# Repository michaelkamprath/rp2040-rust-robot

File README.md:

# RP2040 Rust Robot
Robot controller code in Rust for a two wheel robot driven by a _Raspberry Pi Pico (RP2040)_.

_This is a Work in Progress_

This project is a fork of the [rp2040-project-template](https://github.com/rp-rs/rp2040-project-template). See the template's [README.md](https://github.com/rp-rs/rp2040-project-template/blob/main/README.md) for details on how to build the code found here for the RP2040.

## Notes
Uses [rusty-hook](https://github.com/swellaby/rusty-hook) for precommit hooks.

## Hardware

## License

The contents of this repository are dual-licensed under the _MIT OR Apache
2.0_ License. That means you can chose either the MIT licence or the
Apache-2.0 licence when you re-use this code. See `MIT` or `APACHE2.0` for more
information on each specific licence.

Any submissions to this project (e.g. as Pull Requests) must be made available
under these terms.

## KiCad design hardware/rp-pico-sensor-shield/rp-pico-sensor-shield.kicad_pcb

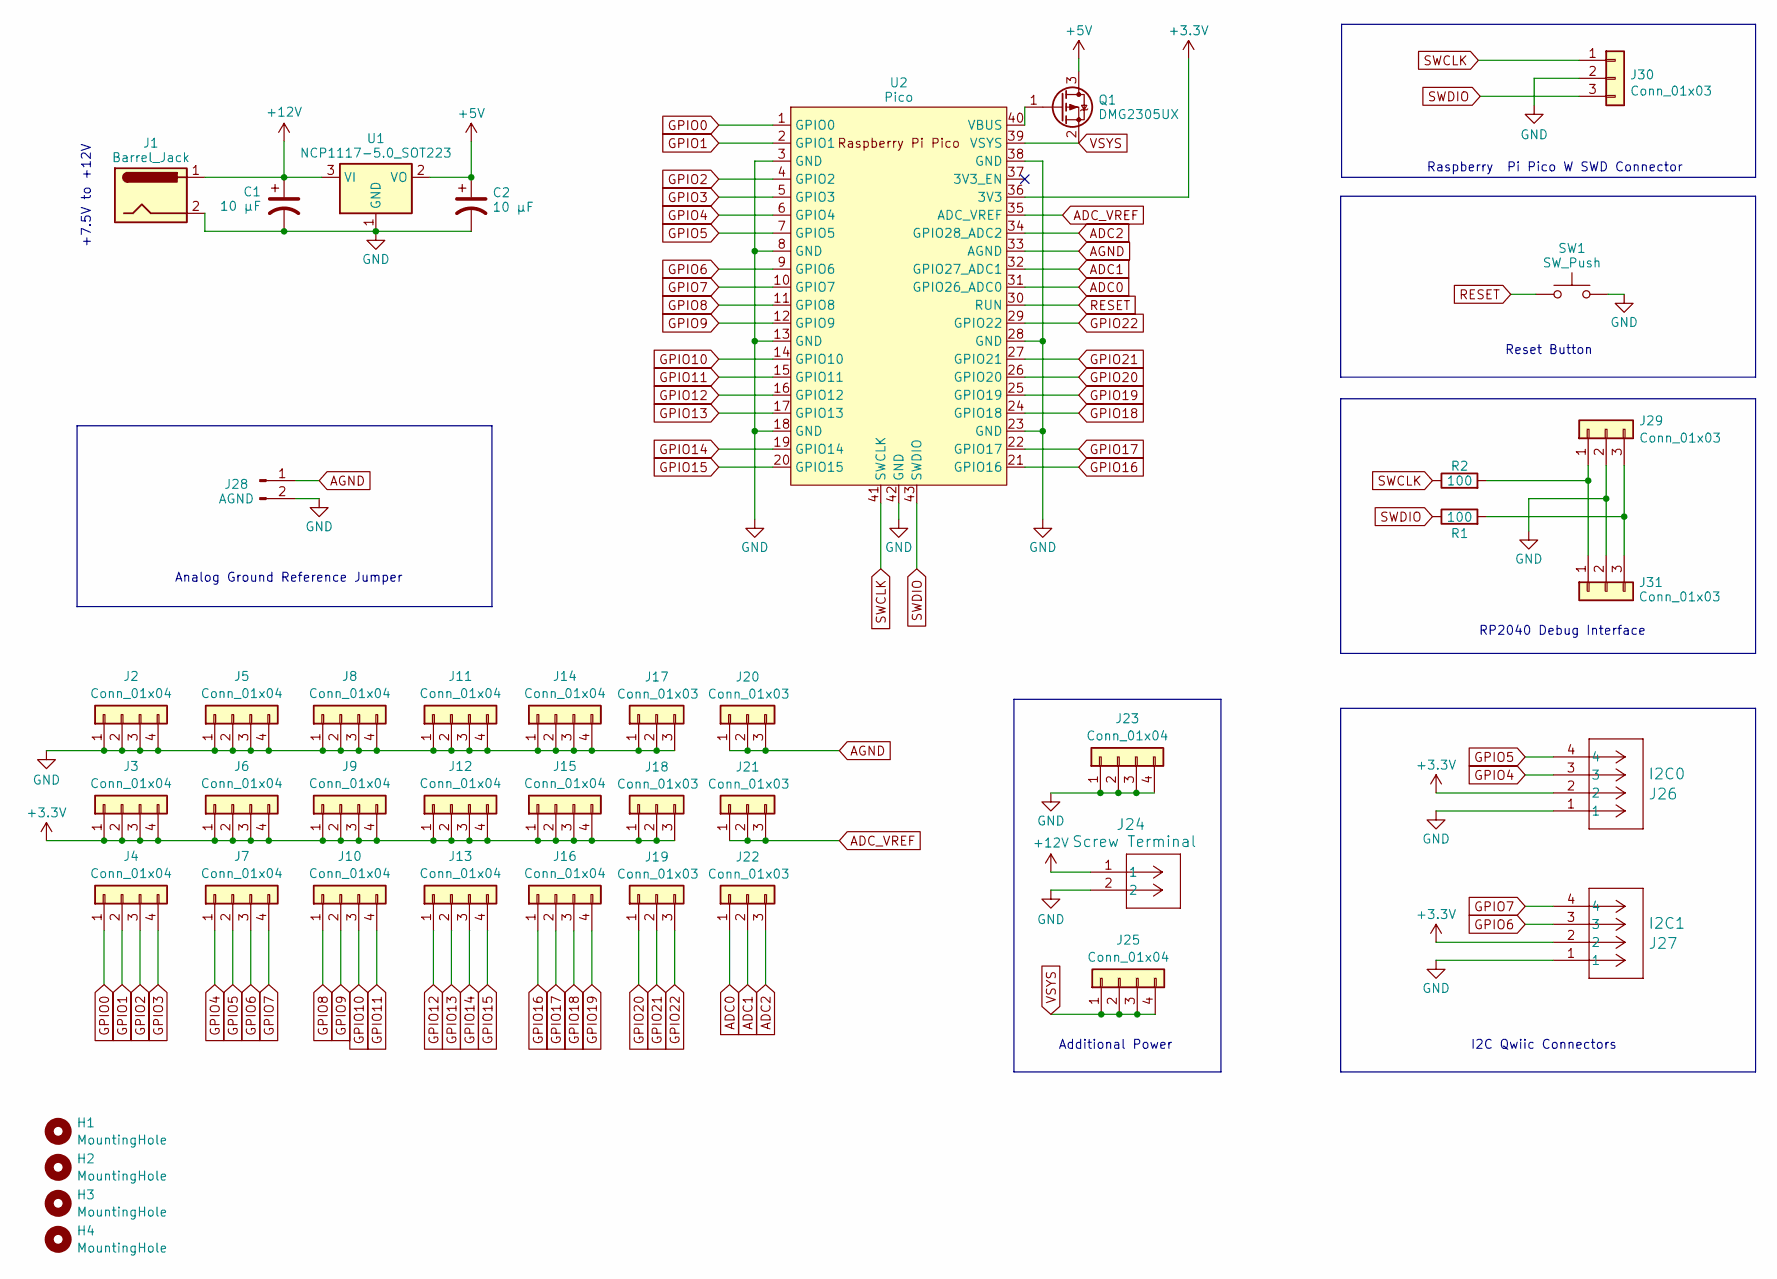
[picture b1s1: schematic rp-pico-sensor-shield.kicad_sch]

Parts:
C1, C2: 10 µF; C_1206_3216Metric_Pad1.33x1.80mm_HandSolder
H1, H2, H3, H4: MountingHole; MountingHole_3.2mm_M3_ISO7380_Pad
J1: Barrel_Jack; BarrelJack_Horizontal
J2, J3, J4, J5, J6, J7, J8, J9, J10, J11, J12, J13, J14, J15, J16, J23, J25: Conn_01x04; PinHeader_1x04_P2.54mm_Vertical
J17, J18, J19, J20, J21, J22: Conn_01x03; PinHeader_1x03_P2.54mm_Vertical
J24: Screw Terminal; CONN2_1760510000_WED
J26: I2C0; CONN_SM04B-SRSS-TB_JST
J27: I2C1; CONN_SM04B-SRSS-TB_JST
J28: AGND; PinHeader_1x02_P2.54mm_Vertical
J29: Conn_01x03; JST_SH_BM03B-SRSS-TB_1x03-1MP_P1.00mm_Vertical
J30: Conn_01x03; PinHeader_1x03_P1.00mm_Vertical
J31: Conn_01x03; PinHeader_1x03_P2.54mm_Horizontal
Q1: DMG2305UX; SOT-23
R1, R2: 100; R_1206_3216Metric_Pad1.30x1.75mm_HandSolder
SW1: SW_Push; SW_PUSH_6mm
U1: NCP1117-5.0_SOT223; SOT-223-3_TabPin2
U2: Pico; RPi_Pico_SMD_TH

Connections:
+3.3V: J3.1, J3.2, J3.3, J3.4, J6.1, J6.2, J6.3, J6.4, J9.1, J9.2, J9.3, J9.4, J12.1, J12.2, J12.3, J12.4, J15.1, J15.2, J15.3, J15.4, J18.1, J18.2, J18.3, J26.2, J27.2, U2.36 (3V3)
+5V: C2.1, Q1.3 (D), U1.2 (VO)
+12V: C1.1, J1.1, J24.1, U1.3 (VI)
ADC0: J22.1, U2.31 (GPIO26_ADC0)
ADC1: J22.2, U2.32 (GPIO27_ADC1)
ADC2: J22.3, U2.34 (GPIO28_ADC2)
ADC_VREF: J21.1, J21.2, J21.3, U2.35 (ADC_VREF)
AGND: J20.1, J20.2, J20.3, J28.1, U2.33 (AGND)
GND: C1.2, C2.2, J1.2, J2.1, J2.2, J2.3, J2.4, J5.1, J5.2, J5.3, J5.4, J8.1, J8.2, J8.3, J8.4, J11.1, J11.2, J11.3, J11.4, J14.1, J14.2, J14.3, J14.4, J17.1, J17.2, J17.3, J23.1, J23.2, J23.3, J23.4, J24.2, J26.1, J27.1, J28.2, J29.2, J30.2, J31.2, SW1.2, U1.1 (GND), U2.3 (GND), U2.8 (GND), U2.13 (GND), U2.18 (GND), U2.23 (GND), U2.28 (GND), U2.38 (GND), U2.42 (GND)
GPIO0: J4.1, U2.1 (GPIO0)
GPIO1: J4.2, U2.2 (GPIO1)
GPIO2: J4.3, U2.4 (GPIO2)
GPIO3: J4.4, U2.5 (GPIO3)
GPIO4: J7.1, J26.3, U2.6 (GPIO4)
GPIO5: J7.2, J26.4, U2.7 (GPIO5)
GPIO6: J7.3, J27.3, U2.9 (GPIO6)
GPIO7: J7.4, J27.4, U2.10 (GPIO7)
GPIO8: J10.1, U2.11 (GPIO8)
GPIO9: J10.2, U2.12 (GPIO9)
GPIO10: J10.3, U2.14 (GPIO10)
GPIO11: J10.4, U2.15 (GPIO11)
GPIO12: J13.1, U2.16 (GPIO12)
GPIO13: J13.2, U2.17 (GPIO13)
GPIO14: J13.3, U2.19 (GPIO14)
GPIO15: J13.4, U2.20 (GPIO15)
GPIO16: J16.1, U2.21 (GPIO16)
GPIO17: J16.2, U2.22 (GPIO17)
GPIO18: J16.3, U2.24 (GPIO18)
GPIO19: J16.4, U2.25 (GPIO19)
GPIO20: J19.1, U2.26 (GPIO20)
GPIO21: J19.2, U2.27 (GPIO21)
GPIO22: J19.3, U2.29 (GPIO22)
unnamed: J29.1, J31.1, R2.2
unnamed: J29.3, J31.3, R1.2
unnamed: Q1.1 (G), U2.40 (VBUS)
RESET: SW1.1, U2.30 (RUN)
SWCLK: J30.1, R2.1, U2.41 (SWCLK)
SWDIO: J30.3, R1.1, U2.43 (SWDIO)
VSYS: J25.1, J25.2, J25.3, J25.4, Q1.2 (S), U2.39 (VSYS)

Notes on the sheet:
I2C Qwiic Connectors
Reset Button
Additional Power
+7.5V to +12V
RP2040 Debug Interface
Analog Ground Reference Jumper
Raspberry Pi Pico W SWD Connector

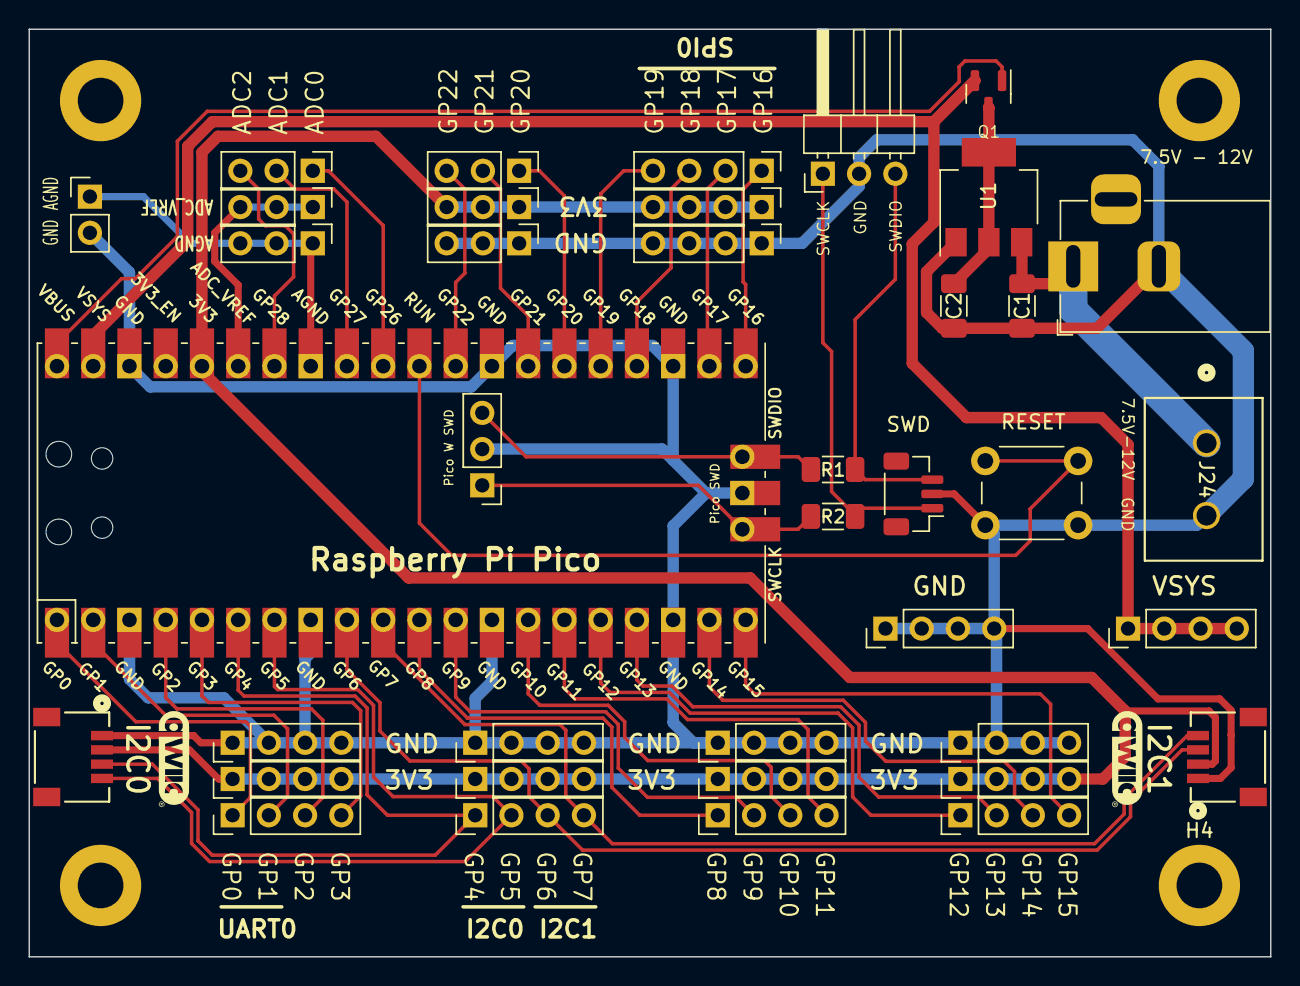
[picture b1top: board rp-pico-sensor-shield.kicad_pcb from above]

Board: 2 copper layers, 87.0 x 65.0 mm, 43 parts (0 on the bottom side), 39 nets.

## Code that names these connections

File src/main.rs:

#![no_std]
#![no_main]
mod driver;
mod model;
mod robot;
mod system;

use core::cell::RefCell;
use critical_section::Mutex;
use defmt::{info, panic};
use defmt_rtt as _;
use panic_probe as _;

use crate::robot::Robot;
use bsp::{
    entry,
    hal::fugit::HertzU32,
    hal::{
        clocks::{init_clocks_and_plls, Clock},
        gpio::{bank0::Gpio25, FunctionI2C, FunctionSioOutput, Pin, PullNone, PullUp},
        multicore::Multicore,
        pac,
        pwm::Slices,
        sio::Sio,
        watchdog::Watchdog,
    },
};
use driver::Driver;
use rp_pico::{self as bsp};
use system::millis::init_millis;
extern crate alloc;

use embedded_alloc::TlsfHeap as Heap;
#[global_allocator]
static HEAP: Heap = Heap::empty();

static GLOBAL_LED_PIN: Mutex<RefCell<Option<Pin<Gpio25, FunctionSioOutput, PullNone>>>> =
    Mutex::new(RefCell::new(None));

#[entry]
fn main() -> ! {
    // Initialize the allocator BEFORE you use it
    {
        use core::mem::MaybeUninit;
        const HEAP_SIZE: usize = 4048;
        static mut HEAP_MEM: [MaybeUninit<u8>; HEAP_SIZE] = [MaybeUninit::uninit(); HEAP_SIZE];
        #[allow(static_mut_refs)]
        unsafe {
            HEAP.init(HEAP_MEM.as_ptr() as usize, HEAP_SIZE)
        }
    }

    info!("Program start");
    let mut pac = pac::Peripherals::take().unwrap();
    let _core = pac::CorePeripherals::take().unwrap();
    let mut watchdog = Watchdog::new(pac.WATCHDOG);
    let mut sio = Sio::new(pac.SIO);

    // External high-speed crystal on the pico board is 12Mhz
    let external_xtal_freq_hz = 12_000_000u32;
    let clocks = init_clocks_and_plls(
        external_xtal_freq_hz,
        pac.XOSC,
        pac.CLOCKS,
        pac.PLL_SYS,
        pac.PLL_USB,
        &mut pac.RESETS,
        &mut watchdog,
    )
    .ok()
    .unwrap();
    let sys_freq = clocks.system_clock.freq();

    let pins = bsp::Pins::new(
        pac.IO_BANK0,
        pac.PADS_BANK0,
        sio.gpio_bank0,
        &mut pac.RESETS,
    );
    critical_section::with(|cs| {
        GLOBAL_LED_PIN
            .borrow(cs)
            .replace(Some(pins.led.reconfigure()));
    });

    // init timer and millis
    let mut timer = rp_pico::hal::Timer::new(pac.TIMER, &mut pac.RESETS, &clocks);
    if let Err(_e) = init_millis(&mut timer) {
        panic!("Error initializing millis");
    }

    // Init & Configure PWMs
    let pwm_slices = Slices::new(pac.PWM, &mut pac.RESETS);
    let mut pwm4 = pwm_slices.pwm4;

    pwm4.set_ph_correct();
    pwm4.enable();

    let mut channel_a = pwm4.channel_a;
    let mut channel_b = pwm4.channel_b;

    channel_a.output_to(pins.gpio8);
    channel_b.output_to(pins.gpio9);

    // Configure two pins as being I²C, not GPIO
    let sda0_pin: Pin<_, FunctionI2C, PullUp> = pins.gpio4.reconfigure();
    let scl0_pin: Pin<_, FunctionI2C, PullUp> = pins.gpio5.reconfigure();
    let sda1_pin: Pin<_, FunctionI2C, PullUp> = pins.gpio6.reconfigure();
    let scl1_pin: Pin<_, FunctionI2C, PullUp> = pins.gpio7.reconfigure();

    // set up I2C
    // let i2c0 = bsp::hal::I2C::new_controller(
    //     pac.I2C0,
    //     sda0_pin,
    //     scl0_pin,
    //     HertzU32::from_raw(400_000),
    //     &mut pac.RESETS,
    //     clocks.system_clock.freq(),
    // );
    // let i2c0_ref_cell = RefCell::new(i2c0);
    // let i2c0_mutex = critical_section::Mutex::new(i2c0_ref_cell);

    let i2c1 = bsp::hal::I2C::new_controller(
        pac.I2C1,
        sda1_pin,
        scl1_pin,
        HertzU32::from_raw(400_000),
        &mut pac.RESETS,
        clocks.system_clock.freq(),
    );
    let i2c1_ref_cell = RefCell::new(i2c1);
    let i2c1_mutex = critical_section::Mutex::new(i2c1_ref_cell);

    // set up SPI
    #[allow(clippy::type_complexity)]
    let spi_mosi = pins.gpio3.into_function::<bsp::hal::gpio::FunctionSpi>();
    let spi_miso = pins.gpio0.into_function::<bsp::hal::gpio::FunctionSpi>();
    let spi_sclk = pins.gpio2.into_function::<bsp::hal::gpio::FunctionSpi>();
    let spi = bsp::hal::spi::Spi::<_, _, _, 8>::new(pac.SPI0, (spi_mosi, spi_miso, spi_sclk));

    // Exchange the uninitialised SPI driver for an initialised one
    let spi = spi.init(
        &mut pac.RESETS,
        clocks.peripheral_clock.freq(),
        HertzU32::from_raw(400_000), // card initialization happens at low baud rate
        embedded_hal::spi::MODE_0,
    );
    let spi_mutex = critical_section::Mutex::new(RefCell::new(spi));

    let sd_card_device = embedded_hal_bus::spi::CriticalSectionDevice::new(
        &spi_mutex,
        pins.gpio1.into_push_pull_output(),
        timer,
    );
    let sd = crate::robot::file_storage::FileStorage::new(sd_card_device, timer);

    // If SD card is successfully initialized, we can increase the SPI speed
    info!(
        "SPI speed increased to {}",
        critical_section::with(|cs| {
            spi_mutex.borrow_ref_mut(cs).set_baudrate(
                clocks.peripheral_clock.freq(),
                HertzU32::from_raw(16_000_000),
            )
        })
        .raw()
    );
    // get core1 ready
    let mut mc = Multicore::new(&mut pac.PSM, &mut pac.PPB, &mut sio.fifo);
    let cores = mc.cores();
    let core1 = &mut cores[1];

    let mut robot = Robot::new(
        pins.gpio10.into_push_pull_output(),
        pins.gpio11.into_push_pull_output(),
        pins.gpio13.into_push_pull_output(),
        pins.gpio12.into_push_pull_output(),
        channel_a,
        channel_b,
        pins.gpio14.into_pull_up_input(),
        pins.gpio15.into_pull_up_input(),
        &i2c1_mutex,
        pins.gpio21.into_pull_up_input(),
        pins.gpio20.into_pull_up_input(),
        sd,
        &mut timer,
        core1,
        sys_freq,
    );

    if let Err(e) = robot.init(sda0_pin, scl0_pin) {
        panic!("Error initializing Robot: {:?}", e);
    }

    let mut driver = Driver::new(robot, timer);

    info!("robot controller and driver created");

    loop {
        driver.handle_loop();
    }
}

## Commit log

2023-12-26 first test build
2023-12-26 added raspberry pi pico sensor shield design
2023-12-27 tweak
2023-12-28 tweaks
2023-12-28 added i2c init
2023-12-29 added pid controller class
    also updated schematic of sensor board to have two IC2 Qwiic connectors
2023-12-29 added git hooks
2023-12-29 remove rusty hook
2023-12-29 added precommit config
2023-12-29 clippy issues
2023-12-30 added wheel encoder interupt support
2023-12-30 added millis utility
2023-12-31 addedsupport for mpu6050 gyro
2023-12-31 removed dev patch
2024-01-03 corrected mpu6050 features
2024-01-06 finalized pin wiring
2024-01-06 wip update to rp2040 sensor shield
2024-01-06 finalized sensor shield design
2024-01-07 updated lcd backpack interface
2024-01-07 added better button debouncing
2024-01-07 added qwiic logo
2024-01-08 restructured project
2024-01-10 documentation update
2024-01-13 refactored to have driver object
2024-01-14 added basic pid controller to straight movement
2024-01-14 removed dev configuration
2024-01-16 added structure for sequenced movement
2024-02-11 updated sensor shield layout
2024-02-12 tweaked trace size
2024-02-18 added turn method
2024-02-18 added ability to traverse a segment in reverse
2024-02-19 basics of sd-card working
2024-02-19 migrated to using shared-bus for I2C
2024-02-19 wip on file system
2024-02-20 added start of log file management
2024-02-20 tweaked turning algorithm
2024-02-24 basics of a logger
2024-02-24 Support for SD Card (#1)
    Implemented basic support for SD card hardware, and a logger that writes to the SD file.
2024-02-24 enabled path file selection and loading
2024-02-24 dtill template for chassis
2024-02-24 added configuration file
2024-02-24 updated cargo.toml
2024-02-25 logging tweaks
2024-02-25 improved logging
2024-02-25 kicad v8 upgrade
2024-02-25 configuration documentation
2024-02-25 updated format
2024-02-25 fixed format
2024-02-25 updated defaults
2024-02-27 added functions menu to onboard UI
2024-05-08 added gyro status display
2024-09-05 test build
2024-09-06 added init check to heading usage
2024-09-06 further testing on spu and i2c bus
2024-09-07 tried critical section devices
2024-09-25 removed inlining config
2024-09-25 fixed inline options and other tweaks
2024-09-29 changed pin type
2024-09-30 switched LCD interface to i2c-character-display
2024-09-30 adjusted logging
2024-09-30 pr fixes
2024-09-30 Upgrade to embedded-hal 1.0 (#2)
    * test build
    * added init check to heading usage
    * further testing on spu and i2c bus
    * tried critical section devices
    * removed inlining config
    * changed pin type
2024-09-30 added straight drive test menu item
2024-09-30 added some test actions
2024-10-07 improved braking and other tweaks
2024-10-25 updated millis count to u64
2024-10-26 improved millis support
2024-11-28 serperated I2C busses for display and gyro
2024-11-29 first semi-working wip for core1
2024-11-29 fully updarted to heading on core 1
2024-11-29 linting issues
2024-11-29 linting issues again
2024-11-29 Move heading calculation to core 1 (#3)
    In order to improve the consistency and reliability of heading calculations, move the work to maintain the heading to the second core on the RP2040, core 1. This required dedicating a I2C bus to each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
    There is no longer an option to calibrate the gyro. Instead, the gyro will always be calibrated on start up if there are no offsets set in the config file (that is, all values are 0), otherwise the o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
2024-11-29 added means to inspect gyro offsets
2024-11-30 updated to use built in LED as gyro readiness indicator
2024-12-07 made the status LED blink while calibrating gyro
2024-12-08 corrected bug in how heading was used when driving straight

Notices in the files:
hardware/rp-pico-sensor-shield/rp-pico-sensor-shield.kicad_pcb:
©2024 by Michael Kamprath
